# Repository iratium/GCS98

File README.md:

# GCS98
A collection of PCB and case designs for a modified 1800 layout I call GCS98.

I enjoy the flexibility of a full-size keyboard, but in my decade or so of using keyboards (including software for general home use, programming, gaming, and engineering work), I have never found a use for certain keys in and around the navigation cluster, namely Page Up, Page Down, Insert, Scroll Lock, Num Lock, and Pause Break. Additionally, the full size layout is not ergonomic in terms of gaming.

I discovered the 96% and 1800 layouts and felt I had discovered the perfect out-of-the-box solution in the 1800 layout specifically, but was disappointed to find that the layout is somewhat rare. My searches led me to the Keychron K4 (with this specific configuration https://www.keychron.com/products/keychron-k4-wireless-mechanical-keyboard-version-2?variant=32287344427097), and after substituting in Glorious Panda Switches for most keys and upgrading to PBT keys for the first time, I finally had a keyboard that felt like mine. Unfortunately, the K4 still has one major drawback being a compact 96% layout as opposed to a proper 1800: the remaining navigation keys, arrow keys, and delete key are not easily accessible by touch. 

To get the last 4% of customization that the compact 96% layout leaves in the aether, the only option forward is to do a fully custom build. I am a mechanical engineer by trade and I am familiar with the kinds of tools to design and manufacture a housed PCB; my specialty is not in electronics though, so I will inevitably be following tutorials and asking for help. 

Feel free to share this project with others, I've already been asked a couple of times whether I'd consider doing a group buy around this layout. You can also contact me over Discord Iratium#4718 or email at gavinshehan@gmail.com.

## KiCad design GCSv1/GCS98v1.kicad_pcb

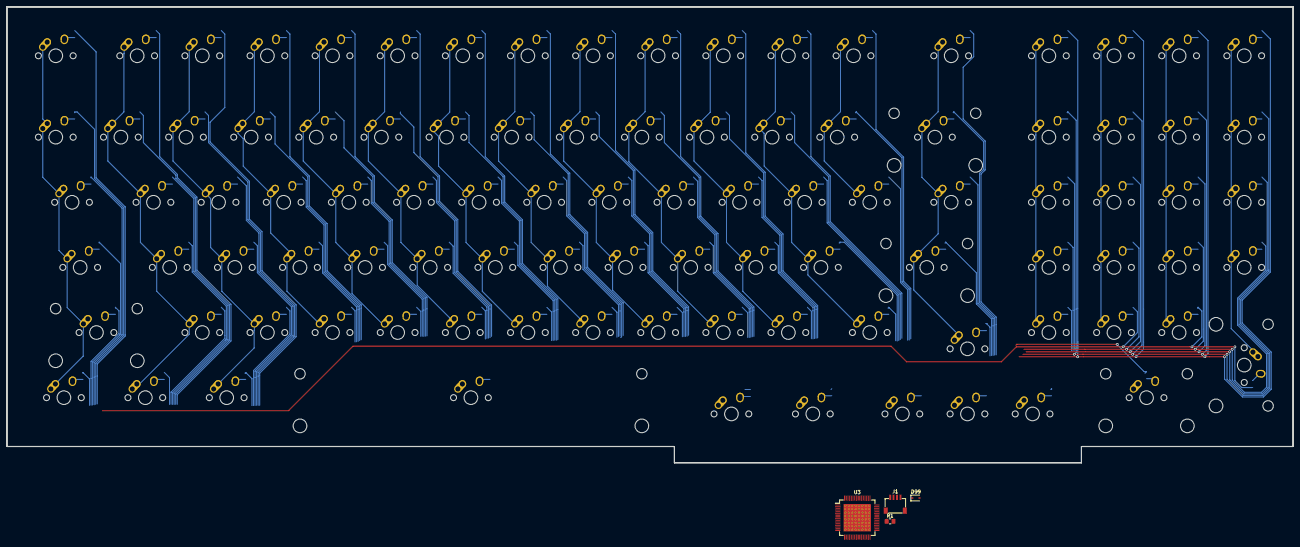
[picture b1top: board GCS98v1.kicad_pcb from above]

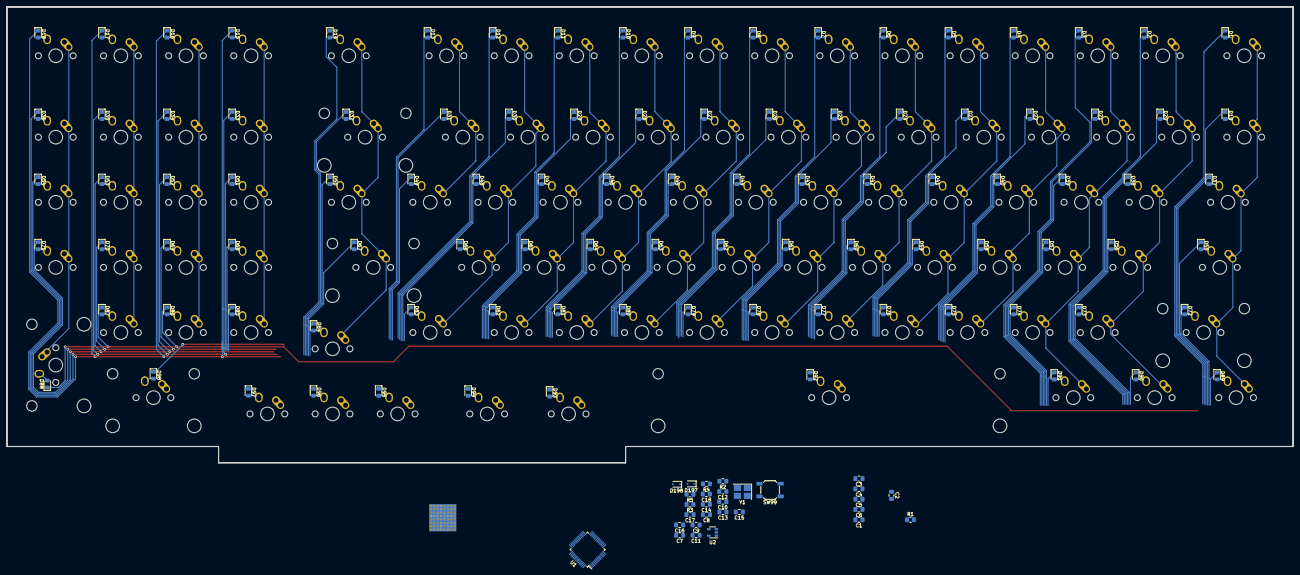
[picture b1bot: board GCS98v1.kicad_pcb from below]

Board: 2 copper layers, 376.2 x 133.3 mm, 229 parts (127 on the bottom side), 136 nets.

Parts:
C1, C2, C3, C4, C5, C6: 100µF; C_0805_2012Metric_Pad1.18x1.45mm_HandSolder
C7: 1µF; C_0805_2012Metric_Pad1.18x1.45mm_HandSolder
C8, C9, C11, C12, C13, C14, C15, C18: 100nF; C_0805_2012Metric_Pad1.18x1.45mm_HandSolder
C10: 10nF; C_0805_2012Metric_Pad1.18x1.45mm_HandSolder
C16, C17: 20pF; C_0805_2012Metric_Pad1.18x1.45mm_HandSolder
D1, D2, D3, D4, D5, D6, D7, D8, D9, D10, D11, D12, D13, D14, D15, D16, D17, D18, D19, D20, D21, D22, D23, D24, D25, D26, D27, D28, D29, D30, D31, D32, D33, D34, D35, D36, D37, D38, D39, D40, D41, D42, D43, D44, D45, D46, D47, D48, D49, D50, D51, D52, D53, D54, D55, D56, D57, D58, D59, D60, D61, D62, D63, D64, D65, D66, D67, D68, D69, D70, D71, D72, D73, D74, D75, D76, D77, D78, D79, D80, D81, D82, D83, D84, D85, D86, D87, D88, D89, D90, D91, D92, D93, D94, D95, D96, D97, D98: D; D_0805_2012Metric_Pad1.15x1.40mm_HandSolder
D99, D197, D198: BAT60A; D_SOD-323
J1: SM04B-SRSS-TB(LF)(SN); JST-SR-4
R1, R5: 1K5; R_0805_2012Metric_Pad1.20x1.40mm_HandSolder
R1#2: 0.5K; R_0805_2012Metric_Pad1.20x1.40mm_HandSolder
R2, R4: 10K; R_0805_2012Metric_Pad1.20x1.40mm_HandSolder
R3: 100K; R_0805_2012Metric_Pad1.20x1.40mm_HandSolder
SW1: ESC; MX-1U-NoLED
SW2: F1; MX-1U-NoLED
SW3: F2; MX-1U-NoLED
SW4: F3; MX-1U-NoLED
SW5: F4; MX-1U-NoLED
SW6: F5; MX-1U-NoLED
SW7: F6; MX-1U-NoLED
SW8: F7; MX-1U-NoLED
SW9: F8; MX-1U-NoLED
SW10: F9; MX-1U-NoLED
SW11: F10; MX-1U-NoLED
SW12: F11; MX-1U-NoLED
SW13: F12; MX-1U-NoLED
SW14: DEL; MX-1.5U-NoLED
SW15: F13; MX-1U-NoLED
SW16: F14; MX-1U-NoLED
SW17: F15; MX-1U-NoLED
SW18: F16; MX-1U-NoLED
SW19: TILDE; MX-1U-NoLED
SW20: 1; MX-1U-NoLED
SW21: 2; MX-1U-NoLED
SW22: 3; MX-1U-NoLED
SW23: 4; MX-1U-NoLED
SW24: 5; MX-1U-NoLED
SW25: 6; MX-1U-NoLED
SW26: 7; MX-1U-NoLED
SW27: 8; MX-1U-NoLED
SW28: 9; MX-1U-NoLED
SW29: 0; MX-1U-NoLED
SW30: DASH; MX-1U-NoLED
SW31: EQUAL; MX-1U-NoLED
SW32: BKSPC; MX-2U-NoLED
SW33: MOP1; MX-1U-NoLED
SW34: MOP2; MX-1U-NoLED
SW35: MOP3; MX-1U-NoLED
SW36: MOP4; MX-1U-NoLED
SW37: TAB; MX-1.5U-NoLED
SW38: Q; MX-1U-NoLED
SW39: W; MX-1U-NoLED
SW40: E; MX-1U-NoLED
SW41: R; MX-1U-NoLED
SW42: T; MX-1U-NoLED
SW43: Y; MX-1U-NoLED
SW44: U; MX-1U-NoLED
SW45: I; MX-1U-NoLED
SW46: O; MX-1U-NoLED
SW47: P; MX-1U-NoLED
SW48: LBRKT; MX-1U-NoLED
SW49: RBRKT; MX-1U-NoLED
SW50: BSLSH; MX-1.5U-NoLED
SW51: NUM7; MX-1U-NoLED
SW52: NUM8; MX-1U-NoLED
SW53: NUM9; MX-1U-NoLED
SW54: MOP5; MX-1U-NoLED
SW55: CAPS; MX-1.75U-NoLED
SW56: A; MX-1U-NoLED
SW57: S; MX-1U-NoLED
SW58: D; MX-1U-NoLED
SW59: F; MX-1U-NoLED
SW60: G; MX-1U-NoLED
SW61: H; MX-1U-NoLED
SW62: J; MX-1U-NoLED
SW63: K; MX-1U-NoLED
SW64: L; MX-1U-NoLED
SW65: SMCLN; MX-1U-NoLED
SW66: APOST; MX-1U-NoLED
SW67: ENTER; MX-2.25U-NoLED
SW68: NUM4; MX-1U-NoLED
SW69: NUM5; MX-1U-NoLED
SW70: NUM6; MX-1U-NoLED
SW71: MOP6; MX-1U-NoLED
SW72: LSHFT; MX-2.25U-NoLED
SW73: Z; MX-1U-NoLED
SW74: X; MX-1U-NoLED
SW75: C; MX-1U-NoLED
SW76: V; MX-1U-NoLED
SW77: B; MX-1U-NoLED
SW78: N; MX-1U-NoLED
SW79: M; MX-1U-NoLED
SW80: COMMA; MX-1U-NoLED
SW81: PRD; MX-1U-NoLED
SW82: SLSH; MX-1U-NoLED
SW83: RSHFT; MX-1.5U-NoLED
SW84: UP; MX-1U-NoLED
SW85: NUM1; MX-1U-NoLED
SW86: NUM2; MX-1U-NoLED
SW87: NUM3; MX-1U-NoLED
SW88: NUMEN; MX-2U-NoLED
SW89: CTRL; MX-1.25U-NoLED
SW90: WIN; MX-1.25U-NoLED
SW91: ALT; MX-1.25U-NoLED
SW92: SPACE; MX-6.25U-NoLED
SW93: HOME; MX-1.25U-NoLED
SW94: END; MX-1.25U-NoLED
SW95: LEFT; MX-1U-NoLED
SW96: DOWN; MX-1U-NoLED
SW97: RIGHT; MX-1U-NoLED
SW98: NUM0; MX-2U-NoLED
SW99: SW_Push; SW_SPST_SKQG_WithStem
U1: STM32F303CCTx; LQFP-48_7x7mm_P0.5mm
U2: LD3985M33R_SOT23; SOT-23-5
U3: TUSB4041I; HTQFP-64-1EP_10x10mm_P0.5mm_EP8x8mm_Mask4.4x4.4mm_ThermalVi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
Y1: 16MHz; Crystal_SMD_3225-4Pin_3.2x2.5mm_HandSoldering

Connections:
+3V3: C12.1, C13.1, C14.1, C15.1, D197.1, R1.1, R5.1, U1.1, U1.9, U1.24, U1.36, U1.48
+5V: C1.1, C2.1, C3.1, C4.1, C5.1, C6.1, C7.1, C9.1, D99.1, D198.1, U2.1, U2.3
BOOT0: R3.1, U1.44
DN1: J1.2, U1.32, U3.34
DP1: J1.3, R1.2, U1.33, U3.33
GND: C1.2, C2.2, C3.2, C4.2, C5.2, C6.2, C7.2, C8.2, C9.2, C10.2, C11.2, C12.2, C13.2, C14.2, C15.2, C16.2, C17.2, C18.2, J1.4, R2.2, R3.2, R4.2, SW99.1, U1.8, U1.23, U1.35, U1.47, U2.2, Y1.2, Y1.4
NRST: C18.1, SW99.2, U1.7
unnamed: C10.1, U2.4
unnamed: C8.1, C11.1, D197.2, U2.5
unnamed: D1.2, SW1.2
unnamed: D2.2, SW2.2
unnamed: D3.2, SW3.2
unnamed: D4.2, SW4.2
unnamed: D5.2, SW5.2
unnamed: D6.2, SW6.2
unnamed: D7.2, SW7.2
unnamed: D8.2, SW8.2
unnamed: D9.2, SW9.2
unnamed: D10.2, SW10.2
unnamed: D11.2, SW11.2
unnamed: D12.2, SW12.2
unnamed: D13.2, SW13.2
unnamed: D14.2, SW14.2
unnamed: D15.2, SW15.2
unnamed: D16.2, SW16.2
unnamed: D17.2, SW17.2
unnamed: D18.2, SW18.2
unnamed: D19.2, SW19.2
unnamed: D20.2, SW20.2
unnamed: D21.2, SW21.2
unnamed: D22.2, SW22.2
unnamed: D23.2, SW23.2
unnamed: D24.2, SW24.2
unnamed: D25.2, SW25.2
unnamed: D26.2, SW26.2
unnamed: D27.2, SW27.2
unnamed: D28.2, SW28.2
unnamed: D29.2, SW29.2
unnamed: D30.2, SW30.2
unnamed: D31.2, SW31.2
unnamed: D32.2, SW32.2
unnamed: D33.2, SW33.2
unnamed: D34.2, SW34.2
unnamed: D35.2, SW35.2
unnamed: D36.2, SW36.2
unnamed: D37.2, SW37.2
unnamed: D38.2, SW38.2
unnamed: D39.2, SW39.2
unnamed: D40.2, SW40.2
unnamed: D41.2, SW41.2
unnamed: D42.2, SW42.2
unnamed: D43.2, SW43.2
unnamed: D44.2, SW44.2
unnamed: D45.2, SW45.2
unnamed: D46.2, SW46.2
unnamed: D47.2, SW47.2
unnamed: D48.2, SW48.2
unnamed: D49.2, SW49.2
unnamed: D50.2, SW50.2
unnamed: D51.2, SW51.2
unnamed: D52.2, SW52.2
unnamed: D53.2, SW53.2
unnamed: D54.2, SW54.2
unnamed: D55.2, SW55.2
unnamed: D56.2, SW56.2
unnamed: D57.2, SW57.2
unnamed: D58.2, SW58.2
unnamed: D59.2, SW59.2
unnamed: D60.2, SW60.2
unnamed: D61.2, SW61.2
unnamed: D62.2, SW62.2
unnamed: D63.2, SW63.2
unnamed: D64.2, SW64.2
unnamed: D65.2, SW65.2
unnamed: D66.2, SW66.2
unnamed: D67.2, SW67.2
unnamed: D68.2, SW68.2
unnamed: D69.2, SW69.2
unnamed: D70.2, SW70.2
unnamed: D71.2, SW71.2
unnamed: D72.2, SW72.2
unnamed: D73.2, SW73.2
unnamed: D74.2, SW74.2
unnamed: D75.2, SW75.2
unnamed: D76.2, SW76.2
unnamed: D77.2, SW77.2
unnamed: D78.2, SW78.2
unnamed: D79.2, SW79.2
unnamed: D80.2, SW80.2
unnamed: D81.2, SW81.2
unnamed: D82.2, SW82.2
unnamed: D83.2, SW83.2
unnamed: D84.2, SW84.2
unnamed: D85.2, SW85.2
unnamed: D86.2, SW86.2
unnamed: D87.2, SW87.2
unnamed: D88.2, SW88.2
unnamed: D89.2, SW89.2
unnamed: D90.2, SW90.2
unnamed: D91.2, SW91.2
unnamed: D92.2, SW92.2
unnamed: D93.2, SW93.2
unnamed: D94.2, SW94.2
unnamed: D95.2, SW95.2
unnamed: D96.2, SW96.2
unnamed: D97.2, SW97.2
unnamed: D98.2, SW98.2
unnamed: D99.2, J1.1
unnamed: R2.1, U1.2
unnamed: R4.1, U1.3
OSC_IN: C17.1, U1.5, Y1.3
OSC_OUT: C16.1, U1.6, Y1.1
col00: SW1.1, SW19.1, SW37.1, SW55.1, SW72.1, SW89.1
col01: SW2.1, SW20.1, SW38.1, SW56.1, SW73.1, SW90.1
col02: SW3.1, SW21.1, SW39.1, SW57.1, SW74.1, SW91.1
col03: SW4.1, SW22.1, SW40.1, SW58.1, SW75.1
col04: SW5.1, SW23.1, SW41.1, SW59.1, SW76.1
col05: SW6.1, SW24.1, SW42.1, SW60.1, SW77.1, SW92.1
col06: SW7.1, SW25.1, SW43.1, SW61.1, SW78.1
col07: SW8.1, SW26.1, SW44.1, SW62.1, SW79.1
col08: SW9.1, SW27.1, SW45.1, SW63.1, SW80.1
col09: SW10.1, SW28.1, SW46.1, SW64.1, SW81.1, SW93.1
col10: SW11.1, SW29.1, SW47.1, SW65.1, SW82.1, SW94.1
col11: SW12.1, SW30.1, SW48.1, SW66.1, SW83.1, SW95.1
col12: SW13.1, SW31.1, SW49.1
col13: SW14.1, SW32.1, SW50.1, SW67.1, SW84.1, SW96.1
col14: SW15.1, SW33.1, SW51.1, SW68.1, SW85.1, SW97.1
col15: SW16.1, SW34.1, SW52.1, SW69.1, SW86.1
col16: SW17.1, SW35.1, SW53.1, SW70.1, SW87.1, SW98.1
col17: SW18.1, SW36.1, SW54.1, SW71.1, SW88.1
row0: D1.1, D2.1, D3.1, D4.1, D5.1, D6.1, D7.1, D8.1, D9.1, D10.1, D11.1, D12.1, D13.1, D14.1, D15.1, D16.1, D17.1, D18.1
row1: D19.1, D20.1, D21.1, D22.1, D23.1, D24.1, D25.1, D26.1, D27.1, D28.1, D29.1, D30.1, D31.1, D32.1, D33.1, D34.1, D35.1, D36.1
row2: D37.1, D38.1, D39.1, D40.1, D41.1, D42.1, D43.1, D44.1, D45.1, D46.1, D47.1, D48.1, D49.1, D50.1, D51.1, D52.1, D53.1, D54.1
row3: D55.1, D56.1, D57.1, D58.1, D59.1, D60.1, D61.1, D62.1, D63.1, D64.1, D65.1, D66.1, D67.1, D68.1, D69.1, D70.1, D71.1
row4: D72.1, D73.1, D74.1, D75.1, D76.1, D77.1, D78.1, D79.1, D80.1, D81.1, D82.1, D83.1, D84.1, D85.1, D86.1, D87.1, D88.1
row5: D89.1, D90.1, D91.1, D92.1, D93.1, D94.1, D95.1, D96.1, D97.1, D98.1

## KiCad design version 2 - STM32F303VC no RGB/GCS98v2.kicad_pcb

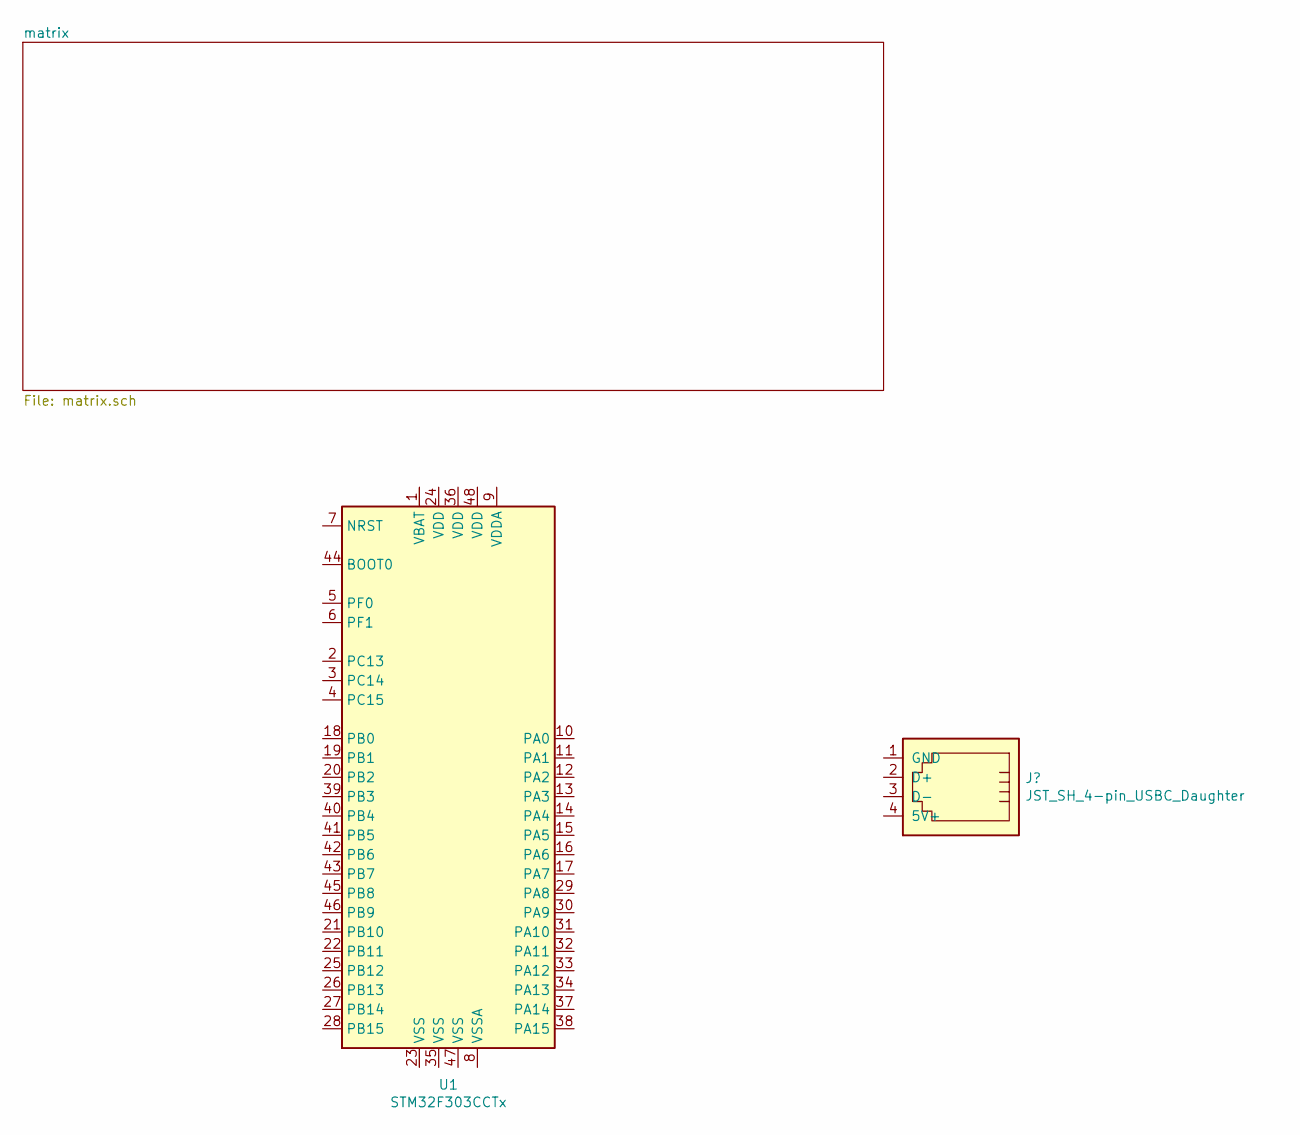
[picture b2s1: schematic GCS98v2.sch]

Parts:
U1: STM32F303CCTx; LQFP-48_7x7mm_P0.5mm

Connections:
+5V: U1.1 (VBAT), U1.9 (VDDA), U1.24 (VDD), U1.36 (VDD), U1.48 (VDD); also elsewhere on the board
GND: U1.8 (VSSA), U1.23 (VSS), U1.35 (VSS), U1.47 (VSS); also elsewhere on the board
unnamed 2: U1.7 (NRST); also elsewhere on the board
unnamed 103: U1.44 (BOOT0); also elsewhere on the board

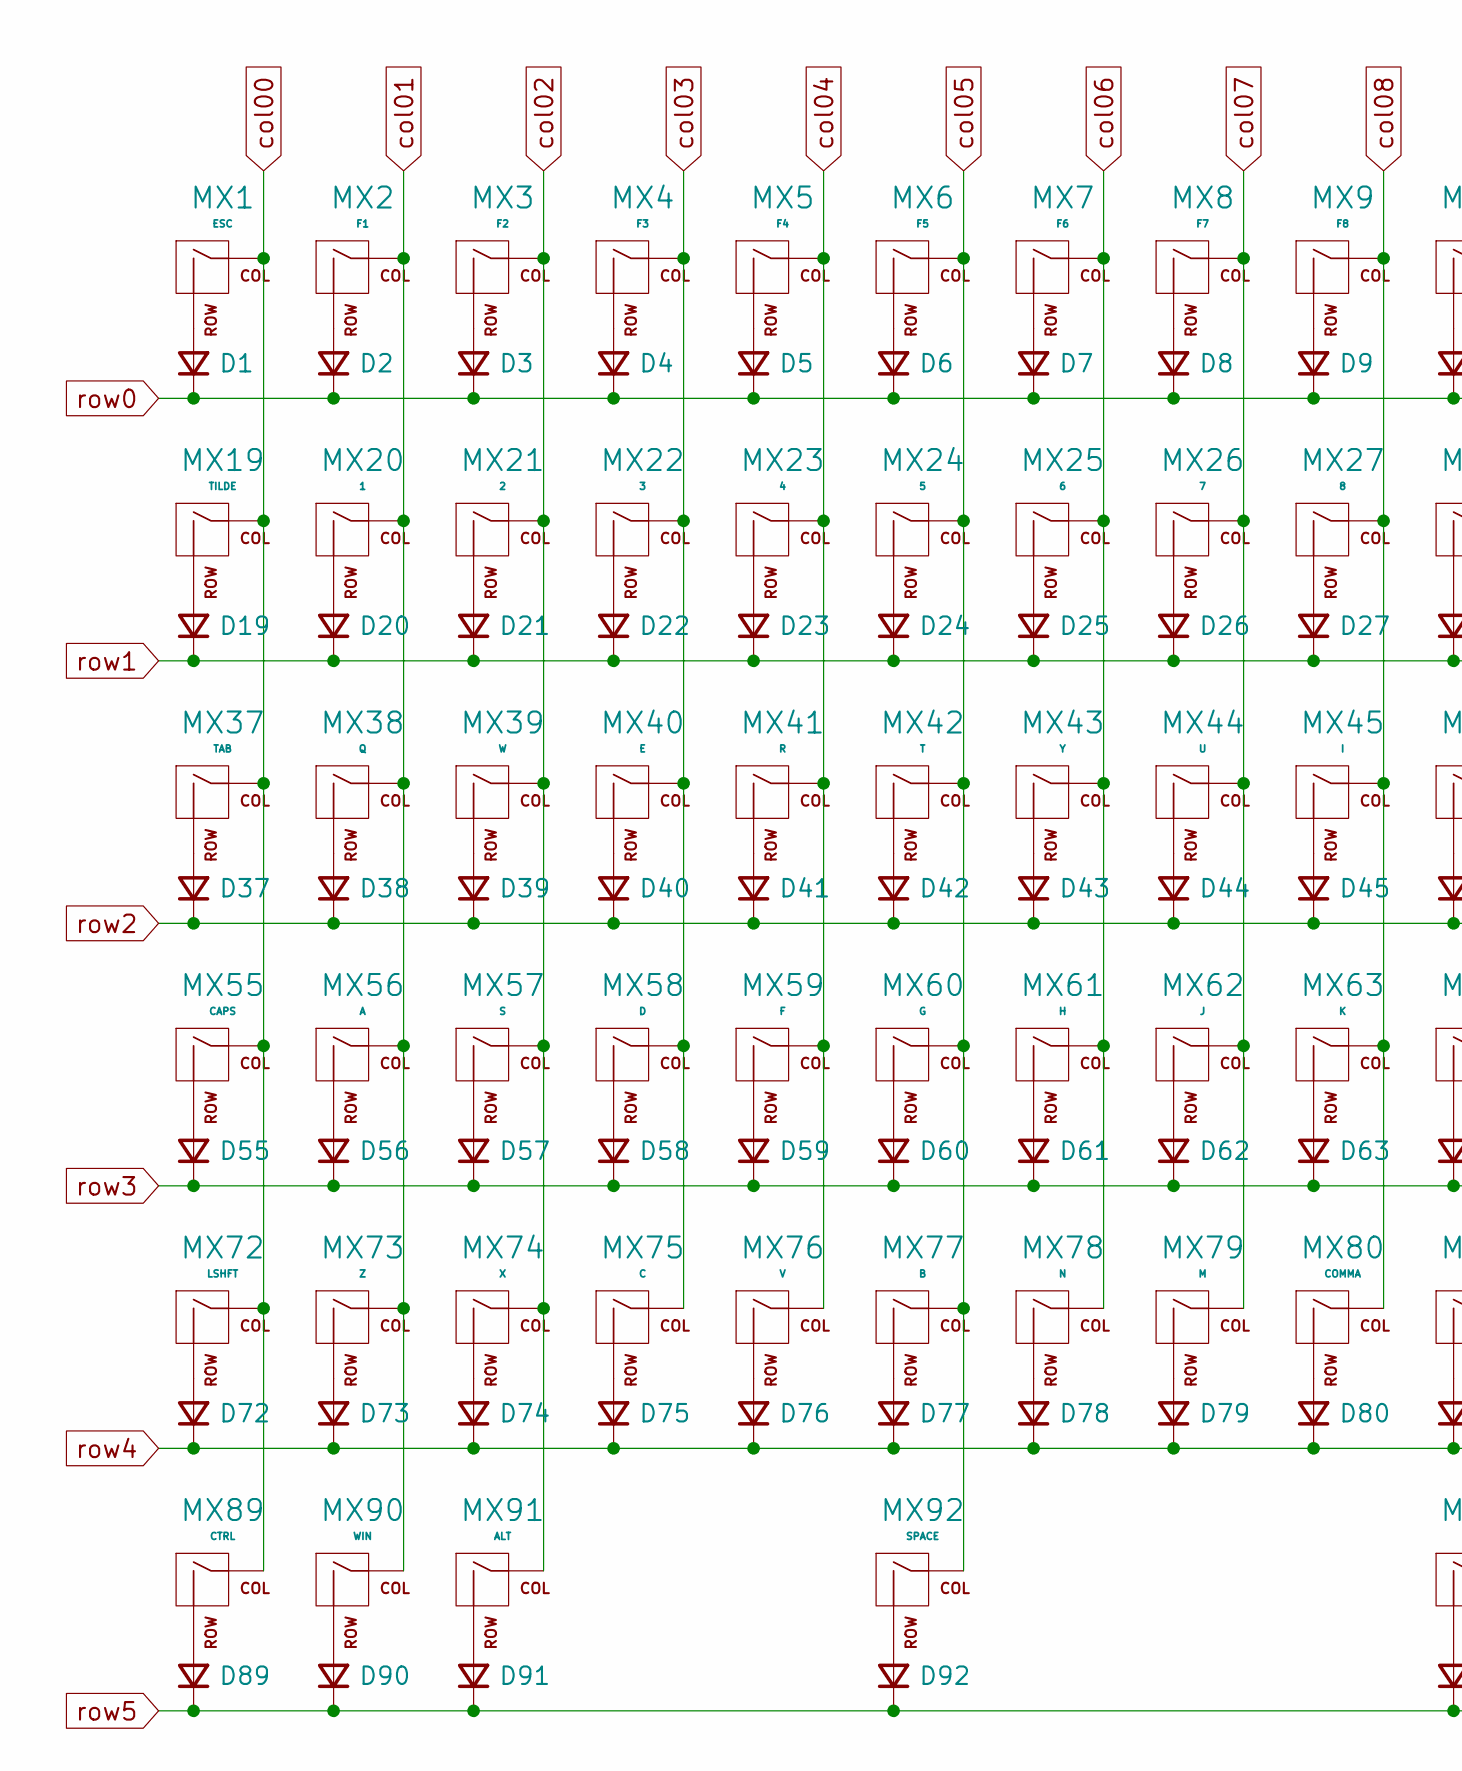
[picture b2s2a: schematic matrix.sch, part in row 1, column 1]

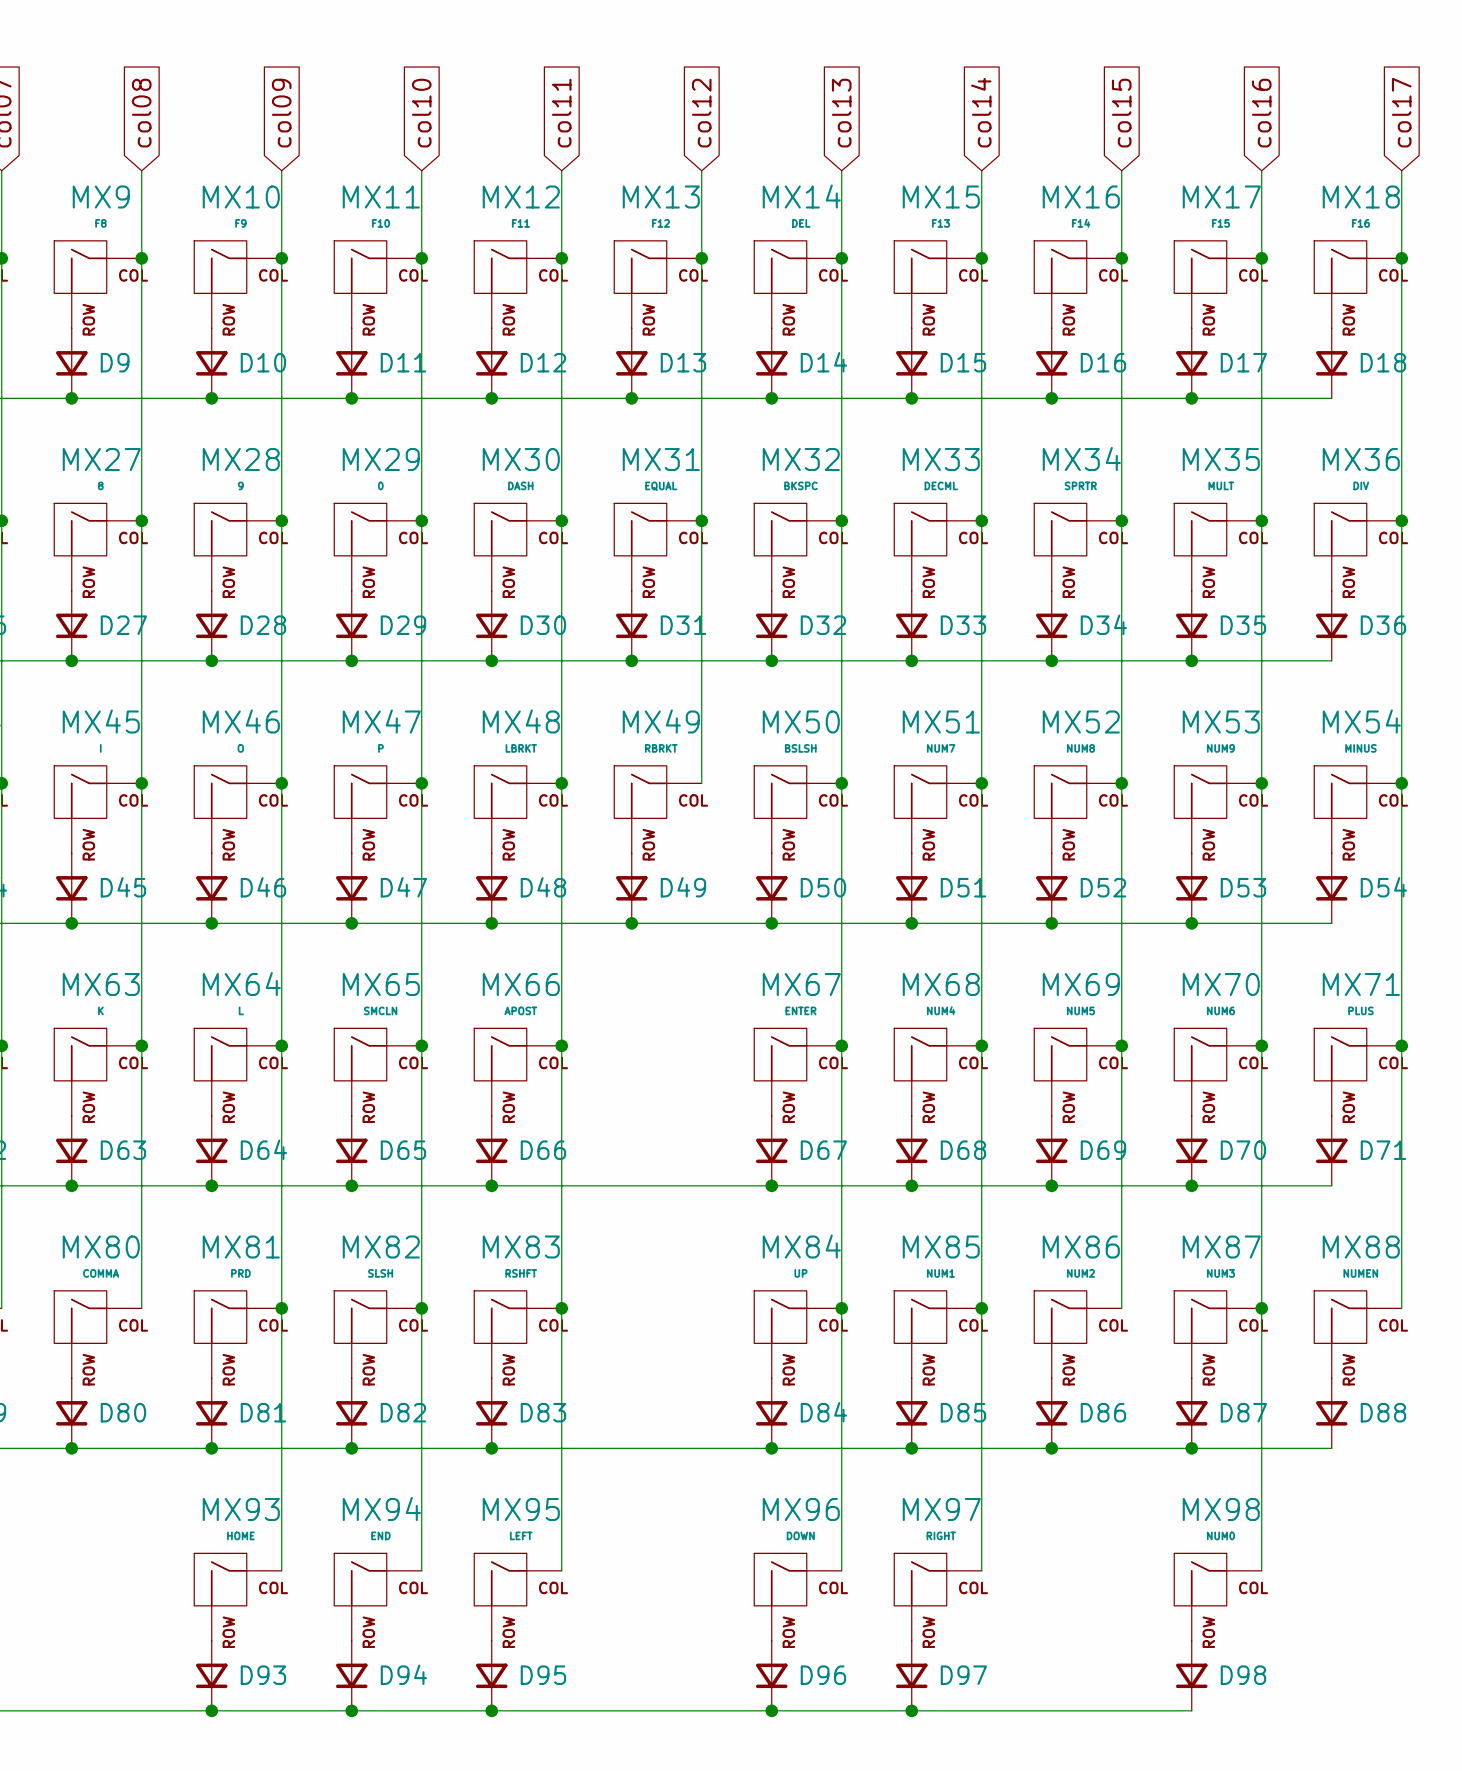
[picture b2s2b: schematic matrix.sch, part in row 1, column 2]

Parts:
D1, D2, D3, D4, D5, D6, D7, D8, D9, D10, D11, D12, D13, D14, D15, D16, D17, D18, D19, D20, D21, D22, D23, D24, D25, D26, D27, D28, D29, D30, D31, D32, D33, D34, D35, D36, D37, D38, D39, D40, D41, D42, D43, D44, D45, D46, D47, D48, D49, D50, D51, D52, D53, D54, D55, D56, D57, D58, D59, D60, D61, D62, D63, D64, D65, D66, D67, D68, D69, D70, D71, D72, D73, D74, D75, D76, D77, D78, D79, D80, D81, D82, D83, D84, D85, D86, D87, D88, D89, D90, D91, D92, D93, D94, D95, D96, D97, D98: D_Small; D_SOD-123
MX1: ESC; MX-1U-NoLED
MX2: F1; MX-1U-NoLED
MX3: F2; MX-1U-NoLED
MX4: F3; MX-1U-NoLED
MX5: F4; MX-1U-NoLED
MX6: F5; MX-1U-NoLED
MX7: F6; MX-1U-NoLED
MX8: F7; MX-1U-NoLED
MX9: F8; MX-1U-NoLED
MX10: F9; MX-1U-NoLED
MX11: F10; MX-1U-NoLED
MX12: F11; MX-1U-NoLED
MX13: F12; MX-1U-NoLED
MX14: DEL; MX-1.5U-NoLED
MX15: F13; MX-1U-NoLED
MX16: F14; MX-1U-NoLED
MX17: F15; MX-1U-NoLED
MX18: F16; MX-1U-NoLED
MX19: TILDE; MX-1U-NoLED
MX20: 1; MX-1U-NoLED
MX21: 2; MX-1U-NoLED
MX22: 3; MX-1U-NoLED
MX23: 4; MX-1U-NoLED
MX24: 5; MX-1U-NoLED
MX25: 6; MX-1U-NoLED
MX26: 7; MX-1U-NoLED
MX27: 8; MX-1U-NoLED
MX28: 9; MX-1U-NoLED
MX29: 0; MX-1U-NoLED
MX30: DASH; MX-1U-NoLED
MX31: EQUAL; MX-1U-NoLED
MX32: BKSPC; MX-2U-NoLED
MX33: DECML; MX-1U-NoLED
MX34: SPRTR; MX-1U-NoLED
MX35: MULT; MX-1U-NoLED
MX36: DIV; MX-1U-NoLED
MX37: TAB; MX-1.5U-NoLED
MX38: Q; MX-1U-NoLED
MX39: W; MX-1U-NoLED
MX40: E; MX-1U-NoLED
MX41: R; MX-1U-NoLED
MX42: T; MX-1U-NoLED
MX43: Y; MX-1U-NoLED
MX44: U; MX-1U-NoLED
MX45: I; MX-1U-NoLED
MX46: O; MX-1U-NoLED
MX47: P; MX-1U-NoLED
MX48: LBRKT; MX-1U-NoLED
MX49: RBRKT; MX-1U-NoLED
MX50: BSLSH; MX-1.5U-NoLED
MX51: NUM7; MX-1U-NoLED
MX52: NUM8; MX-1U-NoLED
MX53: NUM9; MX-1U-NoLED
MX54: MINUS; MX-1U-NoLED
MX55: CAPS; MX-1.75U-NoLED
MX56: A; MX-1U-NoLED
MX57: S; MX-1U-NoLED
MX58: D; MX-1U-NoLED
MX59: F; MX-1U-NoLED
MX60: G; MX-1U-NoLED
MX61: H; MX-1U-NoLED
MX62: J; MX-1U-NoLED
MX63: K; MX-1U-NoLED
MX64: L; MX-1U-NoLED
MX65: SMCLN; MX-1U-NoLED
MX66: APOST; MX-1U-NoLED
MX67: ENTER; MX-2.25U-NoLED
MX68: NUM4; MX-1U-NoLED
MX69: NUM5; MX-1U-NoLED
MX70: NUM6; MX-1U-NoLED
MX71: PLUS; MX-1U-NoLED
MX72: LSHFT; MX-2.25U-NoLED
MX73: Z; MX-1U-NoLED
MX74: X; MX-1U-NoLED
MX75: C; MX-1U-NoLED
MX76: V; MX-1U-NoLED
MX77: B; MX-1U-NoLED
MX78: N; MX-1U-NoLED
MX79: M; MX-1U-NoLED
MX80: COMMA; MX-1U-NoLED
MX81: PRD; MX-1U-NoLED
MX82: SLSH; MX-1U-NoLED
MX83: RSHFT; MX-1.5U-NoLED
MX84: UP; MX-1U-NoLED
MX85: NUM1; MX-1U-NoLED
MX86: NUM2; MX-1U-NoLED
MX87: NUM3; MX-1U-NoLED
MX88: NUMEN; MX-2U-NoLED
MX89: CTRL; MX-1.25U-NoLED
MX90: WIN; MX-1.25U-NoLED
MX91: ALT; MX-1.25U-NoLED
MX92: SPACE; MX-6.25U-NoLED
MX93: HOME; MX-1.25U-NoLED
MX94: END; MX-1.25U-NoLED
MX95: LEFT; MX-1U-NoLED
MX96: DOWN; MX-1U-NoLED
MX97: RIGHT; MX-1U-NoLED
MX98: NUM0; MX-2U-NoLED

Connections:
unnamed: D1.2 (A), MX1.2 (ROW)
unnamed: D2.2 (A), MX2.2 (ROW)
unnamed: D3.2 (A), MX3.2 (ROW)
unnamed: D4.2 (A), MX4.2 (ROW)
unnamed: D5.2 (A), MX5.2 (ROW)
unnamed: D6.2 (A), MX6.2 (ROW)
unnamed: D7.2 (A), MX7.2 (ROW)
unnamed: D8.2 (A), MX8.2 (ROW)
unnamed: D9.2 (A), MX9.2 (ROW)
unnamed: D10.2 (A), MX10.2 (ROW)
unnamed: D11.2 (A), MX11.2 (ROW)
unnamed: D12.2 (A), MX12.2 (ROW)
unnamed: D13.2 (A), MX13.2 (ROW)
unnamed: D14.2 (A), MX14.2 (ROW)
unnamed: D15.2 (A), MX15.2 (ROW)
unnamed: D16.2 (A), MX16.2 (ROW)
unnamed: D17.2 (A), MX17.2 (ROW)
unnamed: D18.2 (A), MX18.2 (ROW)
unnamed: D19.2 (A), MX19.2 (ROW)
unnamed: D20.2 (A), MX20.2 (ROW)
unnamed: D21.2 (A), MX21.2 (ROW)
unnamed: D22.2 (A), MX22.2 (ROW)
unnamed: D23.2 (A), MX23.2 (ROW)
unnamed: D24.2 (A), MX24.2 (ROW)
unnamed: D25.2 (A), MX25.2 (ROW)
unnamed: D26.2 (A), MX26.2 (ROW)
unnamed: D27.2 (A), MX27.2 (ROW)
unnamed: D28.2 (A), MX28.2 (ROW)
unnamed: D29.2 (A), MX29.2 (ROW)
unnamed: D30.2 (A), MX30.2 (ROW)
unnamed: D31.2 (A), MX31.2 (ROW)
unnamed: D32.2 (A), MX32.2 (ROW)
unnamed: D33.2 (A), MX33.2 (ROW)
unnamed: D34.2 (A), MX34.2 (ROW)
unnamed: D35.2 (A), MX35.2 (ROW)
unnamed: D36.2 (A), MX36.2 (ROW)
unnamed: D37.2 (A), MX37.2 (ROW)
unnamed: D38.2 (A), MX38.2 (ROW)
unnamed: D39.2 (A), MX39.2 (ROW)
unnamed: D40.2 (A), MX40.2 (ROW)
unnamed: D41.2 (A), MX41.2 (ROW)
unnamed: D42.2 (A), MX42.2 (ROW)
unnamed: D43.2 (A), MX43.2 (ROW)
unnamed: D44.2 (A), MX44.2 (ROW)
unnamed: D45.2 (A), MX45.2 (ROW)
unnamed: D46.2 (A), MX46.2 (ROW)
unnamed: D47.2 (A), MX47.2 (ROW)
unnamed: D48.2 (A), MX48.2 (ROW)
unnamed: D49.2 (A), MX49.2 (ROW)
unnamed: D50.2 (A), MX50.2 (ROW)
unnamed: D51.2 (A), MX51.2 (ROW)
unnamed: D52.2 (A), MX52.2 (ROW)
unnamed: D53.2 (A), MX53.2 (ROW)
unnamed: D54.2 (A), MX54.2 (ROW)
unnamed: D55.2 (A), MX55.2 (ROW)
unnamed: D56.2 (A), MX56.2 (ROW)
unnamed: D57.2 (A), MX57.2 (ROW)
unnamed: D58.2 (A), MX58.2 (ROW)
unnamed: D59.2 (A), MX59.2 (ROW)
unnamed: D60.2 (A), MX60.2 (ROW)
unnamed: D61.2 (A), MX61.2 (ROW)
unnamed: D62.2 (A), MX62.2 (ROW)
unnamed: D63.2 (A), MX63.2 (ROW)
unnamed: D64.2 (A), MX64.2 (ROW)
unnamed: D65.2 (A), MX65.2 (ROW)
unnamed: D66.2 (A), MX66.2 (ROW)
unnamed: D67.2 (A), MX67.2 (ROW)
unnamed: D68.2 (A), MX68.2 (ROW)
unnamed: D69.2 (A), MX69.2 (ROW)
unnamed: D70.2 (A), MX70.2 (ROW)
unnamed: D71.2 (A), MX71.2 (ROW)
unnamed: D72.2 (A), MX72.2 (ROW)
unnamed: D73.2 (A), MX73.2 (ROW)
unnamed: D74.2 (A), MX74.2 (ROW)
unnamed: D75.2 (A), MX75.2 (ROW)
unnamed: D76.2 (A), MX76.2 (ROW)
unnamed: D77.2 (A), MX77.2 (ROW)
unnamed: D78.2 (A), MX78.2 (ROW)
unnamed: D79.2 (A), MX79.2 (ROW)
unnamed: D80.2 (A), MX80.2 (ROW)
unnamed: D81.2 (A), MX81.2 (ROW)
unnamed: D82.2 (A), MX82.2 (ROW)
unnamed: D83.2 (A), MX83.2 (ROW)
unnamed: D84.2 (A), MX84.2 (ROW)
unnamed: D85.2 (A), MX85.2 (ROW)
unnamed: D86.2 (A), MX86.2 (ROW)
unnamed: D87.2 (A), MX87.2 (ROW)
unnamed: D88.2 (A), MX88.2 (ROW)
unnamed: D89.2 (A), MX89.2 (ROW)
unnamed: D90.2 (A), MX90.2 (ROW)
unnamed: D91.2 (A), MX91.2 (ROW)
unnamed: D92.2 (A), MX92.2 (ROW)
unnamed: D93.2 (A), MX93.2 (ROW)
unnamed: D94.2 (A), MX94.2 (ROW)
unnamed: D95.2 (A), MX95.2 (ROW)
unnamed: D96.2 (A), MX96.2 (ROW)
unnamed: D97.2 (A), MX97.2 (ROW)
unnamed: D98.2 (A), MX98.2 (ROW)
col00: MX1.1 (COL), MX19.1 (COL), MX37.1 (COL), MX55.1 (COL), MX72.1 (COL), MX89.1 (COL)
col01: MX2.1 (COL), MX20.1 (COL), MX38.1 (COL), MX56.1 (COL), MX73.1 (COL), MX90.1 (COL)
col02: MX3.1 (COL), MX21.1 (COL), MX39.1 (COL), MX57.1 (COL), MX74.1 (COL), MX91.1 (COL)
col03: MX4.1 (COL), MX22.1 (COL), MX40.1 (COL), MX58.1 (COL), MX75.1 (COL)
col04: MX5.1 (COL), MX23.1 (COL), MX41.1 (COL), MX59.1 (COL), MX76.1 (COL)
col05: MX6.1 (COL), MX24.1 (COL), MX42.1 (COL), MX60.1 (COL), MX77.1 (COL), MX92.1 (COL)
col06: MX7.1 (COL), MX25.1 (COL), MX43.1 (COL), MX61.1 (COL), MX78.1 (COL)
col07: MX8.1 (COL), MX26.1 (COL), MX44.1 (COL), MX62.1 (COL), MX79.1 (COL)
col08: MX9.1 (COL), MX27.1 (COL), MX45.1 (COL), MX63.1 (COL), MX80.1 (COL)
col09: MX10.1 (COL), MX28.1 (COL), MX46.1 (COL), MX64.1 (COL), MX81.1 (COL), MX93.1 (COL)
col10: MX11.1 (COL), MX29.1 (COL), MX47.1 (COL), MX65.1 (COL), MX82.1 (COL), MX94.1 (COL)
col11: MX12.1 (COL), MX30.1 (COL), MX48.1 (COL), MX66.1 (COL), MX83.1 (COL), MX95.1 (COL)
col12: MX13.1 (COL), MX31.1 (COL), MX49.1 (COL)
col13: MX14.1 (COL), MX32.1 (COL), MX50.1 (COL), MX67.1 (COL), MX84.1 (COL), MX96.1 (COL)
col14: MX15.1 (COL), MX33.1 (COL), MX51.1 (COL), MX68.1 (COL), MX85.1 (COL), MX97.1 (COL)
col15: MX16.1 (COL), MX34.1 (COL), MX52.1 (COL), MX69.1 (COL), MX86.1 (COL)
col16: MX17.1 (COL), MX35.1 (COL), MX53.1 (COL), MX70.1 (COL), MX87.1 (COL), MX98.1 (COL)
col17: MX18.1 (COL), MX36.1 (COL), MX54.1 (COL), MX71.1 (COL), MX88.1 (COL)
row0: D1.1 (K), D2.1 (K), D3.1 (K), D4.1 (K), D5.1 (K), D6.1 (K), D7.1 (K), D8.1 (K), D9.1 (K), D10.1 (K), D11.1 (K), D12.1 (K), D13.1 (K), D14.1 (K), D15.1 (K), D16.1 (K), D17.1 (K), D18.1 (K)
row1: D19.1 (K), D20.1 (K), D21.1 (K), D22.1 (K), D23.1 (K), D24.1 (K), D25.1 (K), D26.1 (K), D27.1 (K), D28.1 (K), D29.1 (K), D30.1 (K), D31.1 (K), D32.1 (K), D33.1 (K), D34.1 (K), D35.1 (K), D36.1 (K)
row2: D37.1 (K), D38.1 (K), D39.1 (K), D40.1 (K), D41.1 (K), D42.1 (K), D43.1 (K), D44.1 (K), D45.1 (K), D46.1 (K), D47.1 (K), D48.1 (K), D49.1 (K), D50.1 (K), D51.1 (K), D52.1 (K), D53.1 (K), D54.1 (K)
row3: D55.1 (K), D56.1 (K), D57.1 (K), D58.1 (K), D59.1 (K), D60.1 (K), D61.1 (K), D62.1 (K), D63.1 (K), D64.1 (K), D65.1 (K), D66.1 (K), D67.1 (K), D68.1 (K), D69.1 (K), D70.1 (K), D71.1 (K)
row4: D72.1 (K), D73.1 (K), D74.1 (K), D75.1 (K), D76.1 (K), D77.1 (K), D78.1 (K), D79.1 (K), D80.1 (K), D81.1 (K), D82.1 (K), D83.1 (K), D84.1 (K), D85.1 (K), D86.1 (K), D87.1 (K), D88.1 (K)
row5: D89.1 (K), D90.1 (K), D91.1 (K), D92.1 (K), D93.1 (K), D94.1 (K), D95.1 (K), D96.1 (K), D97.1 (K), D98.1 (K)

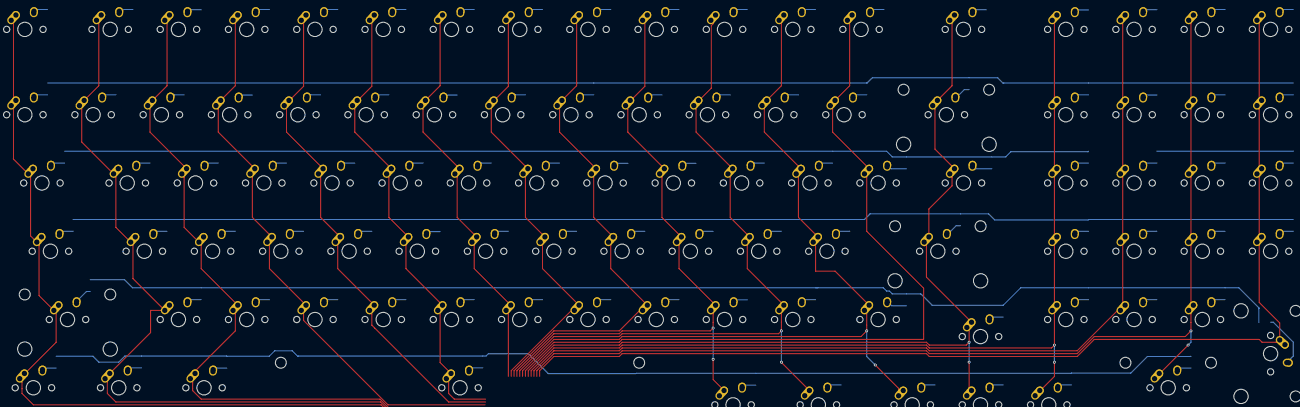
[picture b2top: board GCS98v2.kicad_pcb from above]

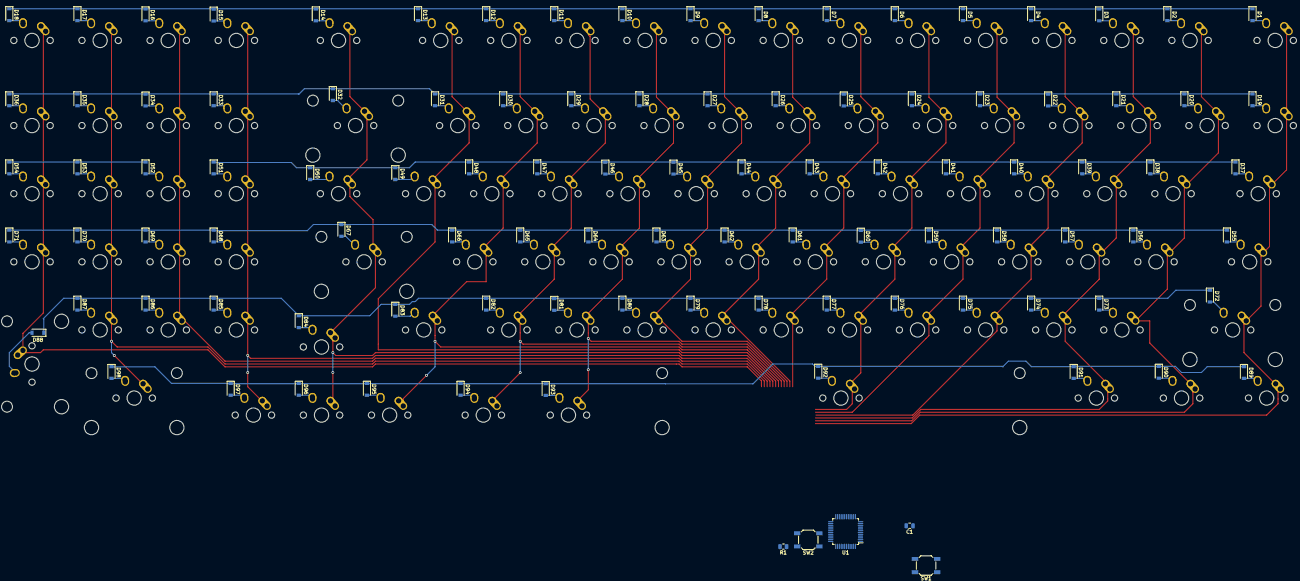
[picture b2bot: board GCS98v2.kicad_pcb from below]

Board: 2 copper layers, 201 parts (103 on the bottom side), 127 nets.

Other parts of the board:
C1: 100nF; C_0805_2012Metric
R1: 10K; R_0805_2012Metric
SW1: SW_Push; SW_SPST_SKQG_WithStem
SW2: SW_Push_SPDT; SW_SPST_SKQG_WithStem

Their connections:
+5V: C1.1; also elsewhere on the board
GND: SW1.1, SW2.1; also elsewhere on the board
unnamed 2: C1.2, SW1.2; also elsewhere on the board
unnamed 103: R1.1; also elsewhere on the board
unnamed: R1.2, SW2.2

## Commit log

2021-07-25 preliminary layout/matrix design
2021-07-25 add switch datasheets, general libraries, and Proton C library
2021-07-25 add libraries to kicad project
2021-07-25 matrix schematic made
2021-07-25 footprint assignments
    Proton C didn't have a footprint available, will need to create a footprint with pin array
2021-07-25 USB-C daughter board libraries added
2021-07-25 project 2 progress save
    Proton C seems to be out of stock everywhere, was gonna make this v2 anyway
2021-07-25 switch and diode layout done
2021-07-26 project corrupted
    system event viewer: "The description for Event ID 1 from source NVIDIA OpenGL Driver cannot be found. Either the component that raises this event is not installed on your local computer or the insta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
    rolling back to previous commit after submitting this one
2021-07-26 Revert "project corrupted"
    This reverts commit 6e2c007335474fac45b2d4a7722601066718bb04.
2021-07-26 Revert "Revert "project corrupted""
    This reverts commit 2cddc3a0d6036266917c26d4d052fe69f0a22bd9.
2021-07-26 columns routed
    updating graphics driver fixed the corruption issue
2021-07-26 column traces inverted to back copper
2021-07-26 rows and columns fully routed to spacebar area
2021-07-26 added TODO for when I pick this back up
    signing off for the night
2021-07-27 just overlay the footprints 4head
    did some digging into switch footprint that can accept many switch types, main ones are Cherry, ALPS, and Kailh low profile. These three encompass most commercially available switches
2021-07-28 check-in for someone to review schematic
    finally understand the reference schematic for the discovery board and basically just copied it, plus some housekeeping changes
2021-07-28 started v1
    MCU schematic 90%-100% done, still trying to figure out how to organize matrix
2021-07-29 Unit A and Unit B btw :)
    tried to finish matrix schematic but the fucking custom symbol is dogshit
2021-07-29 fixed switches in matrix, ready for layout
2021-07-29 pick-and-place simulator
2021-07-30 finished placing switches
2021-07-30 tmp commit to revert
2021-07-30 Revert "tmp commit to revert"
    This reverts commit 719a65f32dae8c11ac86a2bec561b3681ac457b9.
2021-07-30 Revert "Revert "tmp commit to revert""
    This reverts commit c13e2767f99bd62ac667c42d9e0cd8f8c7ddee7e.
2021-07-30 i think i get my edge cuts back?
    all the revert commits I have done thus far is because layout editor crashes, and Event Viewer pointed to "NVIDIA OpenGL Driver" in each instance, and then both schematic and layout editors would cra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
    PSA: the express installation option in the driver installer and GeForce Experience leave a lot of duplicate files for programs to find and incorrectly use, make sure to perform a clean install every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
2021-07-30 RGB edition pick and place machine by Corsair
2021-07-30 matrix pick and place done, now to routing it
2021-07-30 backup before changing symbols
    realized the switch symbol I had been using actually has 4 pins, in two stacks of two (really fucking dumb)
2021-07-30 another backup before changing rgb symbol
2021-07-30 matrix wiring 90% done
    still need to figure out how to get power to LEDs (probably route 5V through top plane, then fill in the rest of the top with ground; not much point to filling bottom plane with ground considering al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
    also need to get rows and columns into buses in the spacebar area, otherwise all that's left is min-maxing the positions of connector, MCU, VRM, resonator, and capacitors/resistors/diodes
2021-08-19 preliminary work on USB hub
    The Texas Instruments USB hub that is currently in there seems like the ticket, but I am still not sure about how USB C connectors will work with the hub IC since it is only for USB 2.0. The main iss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
2021-08-20 going to use two USB C Daughterboards
    after doing some research into connecting a USB C connector to the USB 2.0 hub, I looked at the KiCad project for the Daughterboard and saw that an overcurrent protection circuit, IC, and ferrite bea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
2021-08-28 redid matrix routing, not doing USB daughter board because of parts availability
